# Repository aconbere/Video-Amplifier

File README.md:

# Video-Amplifier

A simple video amplifier designed for use in a SuperGun. The board is a light wrapper around the TI [THS7374](https://www.ti.com/product/THS7374) Video Amplifier. It takes in an RBSs signal from a JAMMA board (0–3V AC swing, 0–5V DC bias, high input impedance: 1–10kΩ) and converts it to consumer set friendly outputs (RGB inputs: 0.7V AC, 0–2V DC bias, at 75 ohms impedance).

The basic idea behind the board is to be configurable to how you want it. The input and outputs are designed as terminal blocks that can take any 20 - 26 AWG wire which makes it easy to connect to just about anything on both sides. In cases where you might be more certain on how you're going to install it, the terminal blocks can easily be omitted and wires soldered directly to the board. Wiring into any standard connector is similarly easy if for instance you wanted to wire in a VGA connector.

This is part of a broader [collection of projects](https://github.com/aconbere/Supergun) to piece by piece build up the components of a supergun.

# Current State

This board has been fabbed via Oshpark, fully assembled, and tested as working.

In future revisions I would like to decouple the power ground from the video ground to increase the potential applications of the board. This seems like a completely reasonable design in the scope of a board focused on JAMMA compatibility where almost always video ground and power ground are coupled. But I realized this flaw when I wanted to power my board via an external source and realized the design wouldn't work.

# How to build

## Board fabrication

The project root contains a `.pcb` and a `.bom` file. The pcb files defines the board geometry and traces. Popular fabricator Oshpark offers the ability to submit the `.pcb` file directly to them for manufacturing. To have three boards produced should cost about $16 as of writing this. If people have experience with submitting KiCad projects to other manufacturers (I tested producing gerber outputs with pcbnew and it seemed fine) I would be happy to expand these instructions.

## Bill of Materials

The BOM file or "Bill of Materials" lists a suggested set of parts and links to buy those parts on mouser.com (correct at time of publishing). You expect the cost per board of materials to run you about $7.

If you don't have them already you will also need a JAMMA harness and an arcade power supply. Both of these can be easily purchased online, or in the case of the JAMMA harness assembled. I've provided links to examples below (I don't vouch for these products but want to give folks an easy way to understand what kinds of products are required).

* [JAMMA Harness](https://www.ebay.com/itm/JAMMA-Mame-Cabinet-Wiring-Harness-Loom-Multicade-Arcade-Video-Game-PCB-cable/332418279009)
* [Power Supply](https://www.ebay.com/itm/Happ-15-AMP-Switching-Power-Supply-Arcade-Multicade-8-Liner-Games/123679840929)

## Assembly

Note: The boards will come rough, take the time to grab a little sand paper and smooth the edges before beginning.

The approach we'll take to assembly will try to minimize the amount of time and work required before we can test the work. With some minor deviations, we will start at the top right and work our way left to right and then top to bottom.

### Materials

* Everything in the BOM + JAMMA + Power Supply
* Soldering Iron
* Solder
* Tweezers
* 2 feet of 20 - 24 AWG wire

### Step 1: THS7374

Might as well get the hard part out of the way first and this is it. Besides you'll want room to do this and don't want anything in your way. It's unfortunate that the THS7374 is only sold in surface mount packages and hand soldering surface mount components is a pain. I recommend a pair of fine tweezers, lots of flux, and the "drag" method. [This video](http://www.youtube.com/watch?v=hoLf8gvvXXU&t=5m0s) from eevblog demonstrates the method starting around the 5 minute mark.

## Step 2: Imputs and Outputs

I've set up the board to be built with terminal blocks for signal inputs and outputs and a 2 pin JST connector as 5v power. On the left is a 4 pin terminal block for the 4 input signals (Red, Green, Blue, and Sync) and the 2 pin JST power connector. On the right is a 5 pin terminal block connector for the outputs and ground (Red, Green, Blue, Sync, and Ground).

One little caveat is that at least with the harness that I purchased there isn't an easy way to tap 5v off the supply. In my case I removed a little bit of heat shrink tubing that was protecting the 5v pins on the JAMMA connector and soldered a little line off of that for power.

### Step 2: Red + Green

Technically you could order your signals any way you like, but I always stick with Red, Green, Blue, Sync. In this step we'll put in the top two signal lines Red and Green. Each line consists of a 1K Ohm resistor, a 390 Ohm resistor, a small 0.1uf coupling capacitor, a 75 Ohm resistor, and a 330uf electrolytic capacitor (Note: these are polarized please pat attention to the markings on the board). When both the Red and Green lines are assembled we can move onto our first test.

### Step 3: First test

In order to run a good test we need both a color signal and sync (read more on [component video](https://en.wikipedia.org/wiki/Component_video#RGB_analog_component_video)), without the sync signal you'll end up with a garbled picture. While in the last step we assembled the Red and Green signal lines, the reality is that every signal is handled exactly the same, so we can just attach the sync signal to green to get a test going.

* Solder a line from +5v off the JAMMA connector and attach it to your JST terminal. I crimped my own, but these can be easily purchased with some pre-tinned wires. If this is all a hassle you can just solder into the board directly (the right hand via is positive).
* Snip off the ends of the Red and Sync lines from the JAMMA harness and wired them into the terminal blocks on the left
* Connect the output terminals: Red, Sync, and Ground to your TV
* Power on the TV
* Power on the board

If everything is set up right you should get the image from your board but only in Red.

### Wrapping up

If the test went well, procede copying Step 2 for the remaining signals Blue, and Sync. Test along the way as you feel comfortable

# Contributing

Honestly, I have no experience managing KiCad projects in an opensource community. I can tell from my edits that there can be a large blast radius in a diff from a small observable change. This is something we'll have to work through together. If you have changes you'd like to see, make a PR and we'll work through it together.

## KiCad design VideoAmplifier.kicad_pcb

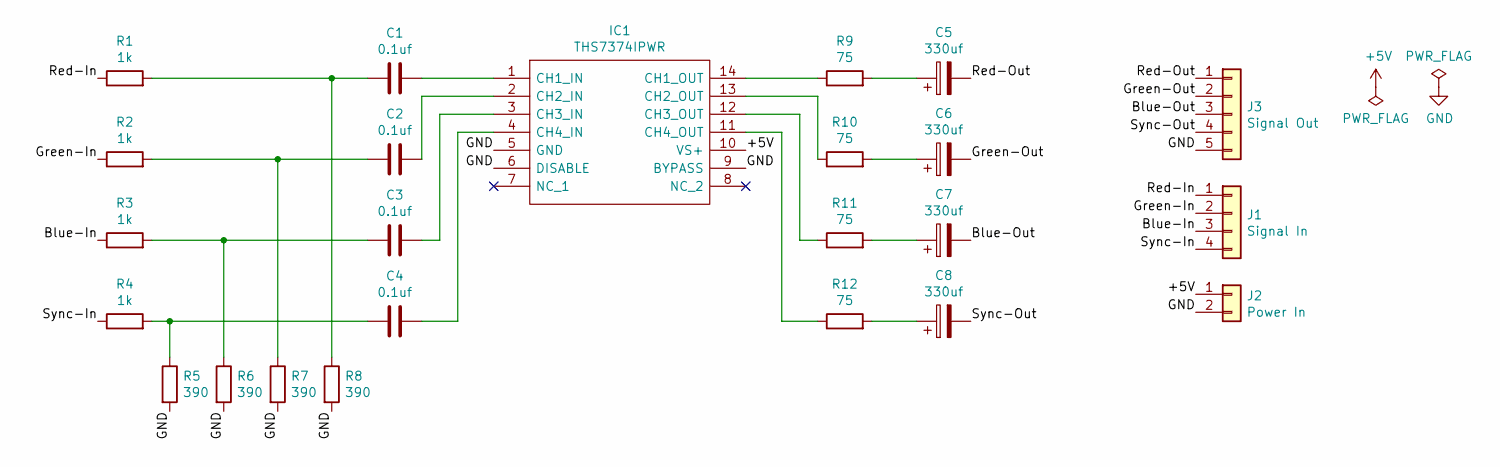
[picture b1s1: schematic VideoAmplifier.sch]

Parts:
C1, C2, C3, C4: 0.1uf; K104M15X7RF53L2
C5, C6, C7, C8: 330uf; CP_Radial_D6.3mm_P2.50mm
IC1: THS7374IPWR; SOP65P640X120-14N; Mouser Part Number 595-THS7374IPWR
J1: Signal In; TB00150004BE
J2: Power In; JST_XH_B2B-XH-AM_1x02_P2.50mm_Vertical
J3: Signal Out; TB003500P05BE
R1, R2, R3, R4: 1k; R_Axial_DIN0204_L3.6mm_D1.6mm_P5.08mm_Horizontal
R5, R6, R7, R8: 390; R_Axial_DIN0204_L3.6mm_D1.6mm_P5.08mm_Horizontal
R9, R10, R11, R12: 75; R_Axial_DIN0204_L3.6mm_D1.6mm_P5.08mm_Horizontal

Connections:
+5V: IC1.10 (VS+), J2.1
/Blue-In: J1.3, R3.1
/Blue-Out: C7.2, J3.3
/Green-In: J1.2, R2.1
/Green-Out: C6.2, J3.2
/Red-In: J1.1, R1.1
/Red-Out: C5.2, J3.1
/Sync-In: J1.4, R4.1
/Sync-Out: C8.2, J3.4
GND: IC1.5 (GND), IC1.6 (DISABLE), IC1.9 (BYPASS), J2.2, J3.5, R5.2, R6.2, R7.2, R8.2
unnamed: C1.1, R1.2, R8.1
unnamed: C1.2, IC1.1 (CH1_IN)
unnamed: C2.1, R2.2, R7.1
unnamed: C2.2, IC1.2 (CH2_IN)
unnamed: C3.1, R3.2, R6.1
unnamed: C3.2, IC1.3 (CH3_IN)
unnamed: C4.1, R4.2, R5.1
unnamed: C4.2, IC1.4 (CH4_IN)
unnamed: C5.1, R9.2
unnamed: C6.1, R10.2
unnamed: C7.1, R11.2
unnamed: C8.1, R12.2
unnamed: IC1.11 (CH4_OUT), R12.1
unnamed: IC1.12 (CH3_OUT), R11.1
unnamed: IC1.13 (CH2_OUT), R10.1
unnamed: IC1.14 (CH1_OUT), R9.1

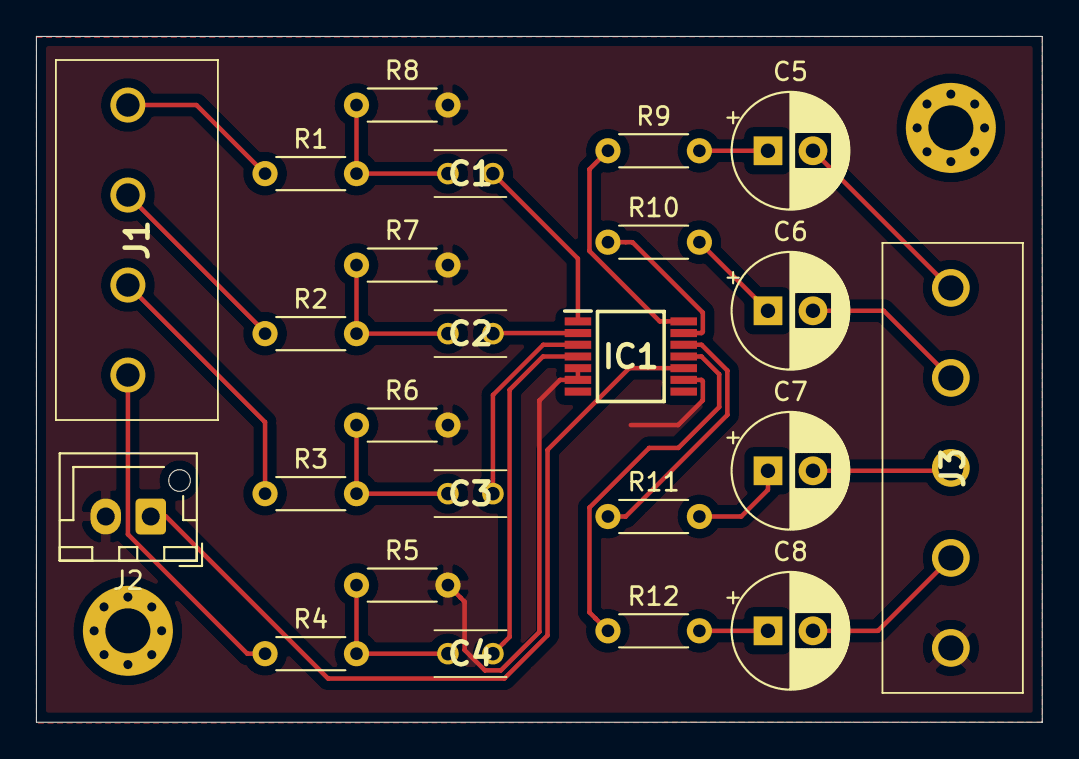
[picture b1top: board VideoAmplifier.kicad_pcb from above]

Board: 2 copper layers, 55.9 x 38.1 mm, 24 parts (0 on the bottom side), 26 nets.

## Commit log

2020-06-20 Simple video amp
2020-06-21 adding text to the back of the board
2020-07-31 updates for printing
    added mounting holes, made the tolerances a bit tighter.
2020-08-02 update track clearances for oshpark
2020-08-23 add preview image
2020-08-23 Add assembled board picture and sample of work
2020-08-23 Add pictures
2020-08-23 Add ln assemble instructions
2020-08-23 Add BOM
